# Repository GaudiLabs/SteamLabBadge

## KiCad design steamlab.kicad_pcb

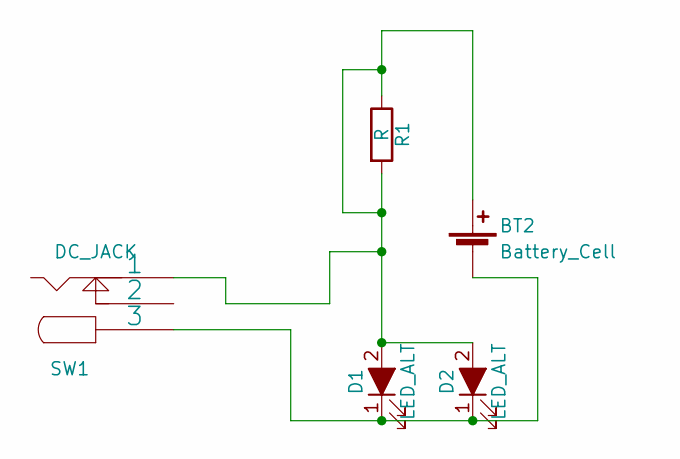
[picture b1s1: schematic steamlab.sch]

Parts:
BT2: Battery_Cell; CR2032_Holder
D1, D2: LED_ALT; TopLed_BitBadge_blink
R1: R; R_1210_HandSoldering
SW1: DC_JACK; PLUG3_5_SMD

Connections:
unnamed: BT2.1 (+), D1.2 (A), D2.2 (A), R1.1, R1.2, SW1.1
unnamed: BT2.2 (-), D1.1 (K), D2.1 (K), SW1.3

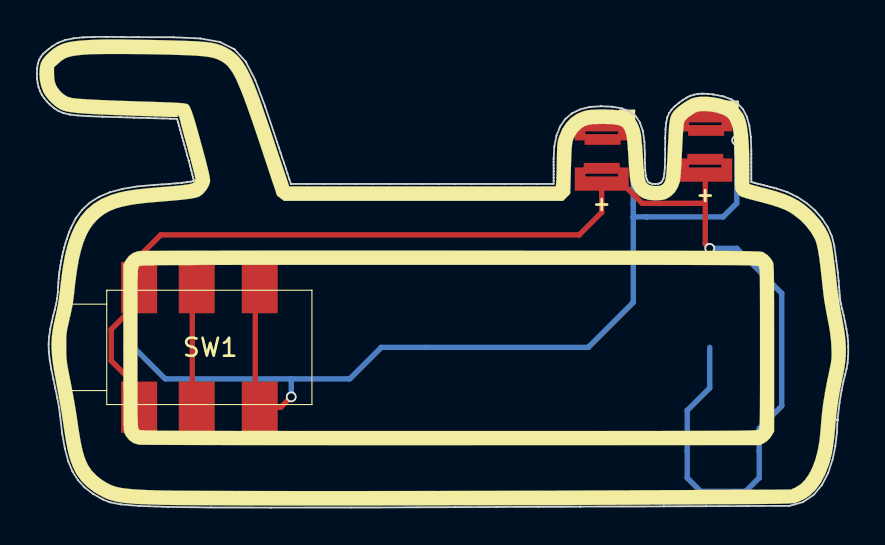
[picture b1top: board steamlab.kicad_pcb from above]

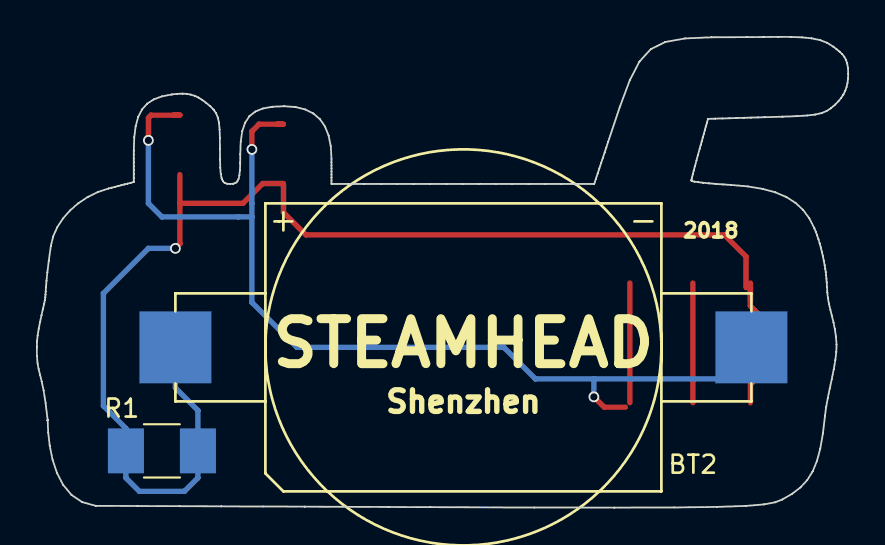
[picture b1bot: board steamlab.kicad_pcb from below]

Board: 2 copper layers, 45.1 x 26.2 mm, 5 parts (2 on the bottom side), 2 nets.

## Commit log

2018-11-05 First push
